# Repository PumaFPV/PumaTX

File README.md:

# PumaTX

THIS README IS NOT UP TO DATE

# Introduction:
This is a try to build my own FPV remote controller based on ESP32 (nRF52 later on) and DJI GL200A for its compactness and format.

# Release Candidates:

RC04: 
	Software:
		PPM
		SBus
		Hall Effect
		Pots reading (Left pot mode switch left = down ; Right = up ; RTH = overwrite)
		Arm reading
		Pre reading
		RTH reading
		Power on / off via sport switch
		basic screen use + vbat + splash screen
		
	Hardware:
		Micro USB (from controller)
		2S LiPo
		external RF (R9M)
		USB 2.0 (or 3.0 if I find one,) to plug in module (gnd, 5v, VBat, Tx)
		Support for JR module in phone holder
		
RC05:
	Software:
		Interupts for buttons (so code can run faster)
		MavLink (only rc, no telemetry) 
§		MavLink Bluetooth Passthrough (Uses to much memory, will have to sort it out for another release)
§		Choice between SBus and MavLink when compiling
		SoftPower use only interrupt
§		LED for power
		
	Hardware:
§		1S battery + USB charger + boost converter
§		MavLink module
		
RC06:
	Software:
		Menu Navigation
		
	Hardware:
		Turn on / off stuff (transistor & MOSFET)
		Fan
		Haptic
		
RC07:
	Software:
		Bluetooth HID
		
RC08:
	Software:
		MavLink telemetry screen

RC09:
	Software:
		CVBS Screen
		
	Hardware:
		USB 3.0 (5v, gnd, tx, rx, vid, 1, 2, VBat)
	
RC10:
	Hardware:
		Homemade PCB
		C1, C2
		Haptic
		
Other ideas:
	SPort
	FrSky X for bind / Rx num
	Sound output
	External bluetooth joystick
	Fix the calibration issue
	Remove screen loop
	eepron save
	
# Required specs:
-Read data from the hall effect MLX sensors from the controller

-Have 10 channels (can't do more cause of the limitation of the controller)

-Output SBus (to plug into R9M)

-Input SPort to read telemetry data (From R9M)

-Have a screen for minimal setup

-Have a Soft Power capabilty (using the power button from the controller)

This is the bare minimum. But I do have way more ideas coming.

# Folders:
In the "PumaTX_RC" folder you will find the different Release Candidate (Higher is better but could be unstable, read description for more details).

In the "Other" folder you will find different kind of "documentation" it is mostly here for my personnal use, as a reference.

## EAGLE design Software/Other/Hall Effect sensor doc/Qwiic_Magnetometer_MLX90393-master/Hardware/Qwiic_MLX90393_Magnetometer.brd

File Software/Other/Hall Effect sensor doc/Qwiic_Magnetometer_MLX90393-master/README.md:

SparkFun Qwiic Magnetometer MLX90393
========================================

[*SparkFun Qwiic Magnetometer MLX90393 (14571)*](https://www.sparkfun.com/products/14571)

The SparkFun MLX90393 Magnetometer Breakout is a triple-axis magnetic sensor board capable of sensing very small fields (like the Earth’s magnetic field), while still behaving as one would expect during saturation in larger fields (like a nearby magnet). The MLX90393 breakout can be used as a compass sensor but also works well as a non-contact controller, a flow meter with a magnetic impeller, or a linear actuator position sensor. To make it even easier to to get your readings, all communication is enacted exclusively via I2C, utilizing our handy Qwiic system. However, we still have broken out 0.1"-spaced pins in case you prefer to use a breadboard.

Repository Contents
-------------------

* **/Hardware** - Eagle design files (.brd, .sch)
* **/Production** - Production panel files (.brd)
* **/Software** - Example Code

Documentation
--------------
* **[Arduino Library](https://github.com/tedyapo/arduino-MLX90393)** - Arduino library MLX90393 magnetometer sensor.
* **[Hookup Guide](https://learn.sparkfun.com/tutorials/qwiic-magnetometer-mlx90393-hookup-guide)** - Basic hookup guide for the SparkFun Qwiic Magnetometer MLX90393.
* **[SparkFun Fritzing repo](https://github.com/sparkfun/Fritzing_Parts)** - Fritzing diagrams for SparkFun products. 

License Information
-------------------

This product is _**open source**_! 

Please review the LICENSE.md file for license information. 

If you have any questions or concerns on licensing, please contact techsupport@sparkfun.com.

Distributed as-is; no warranty is given.

- Your friends at SparkFun.

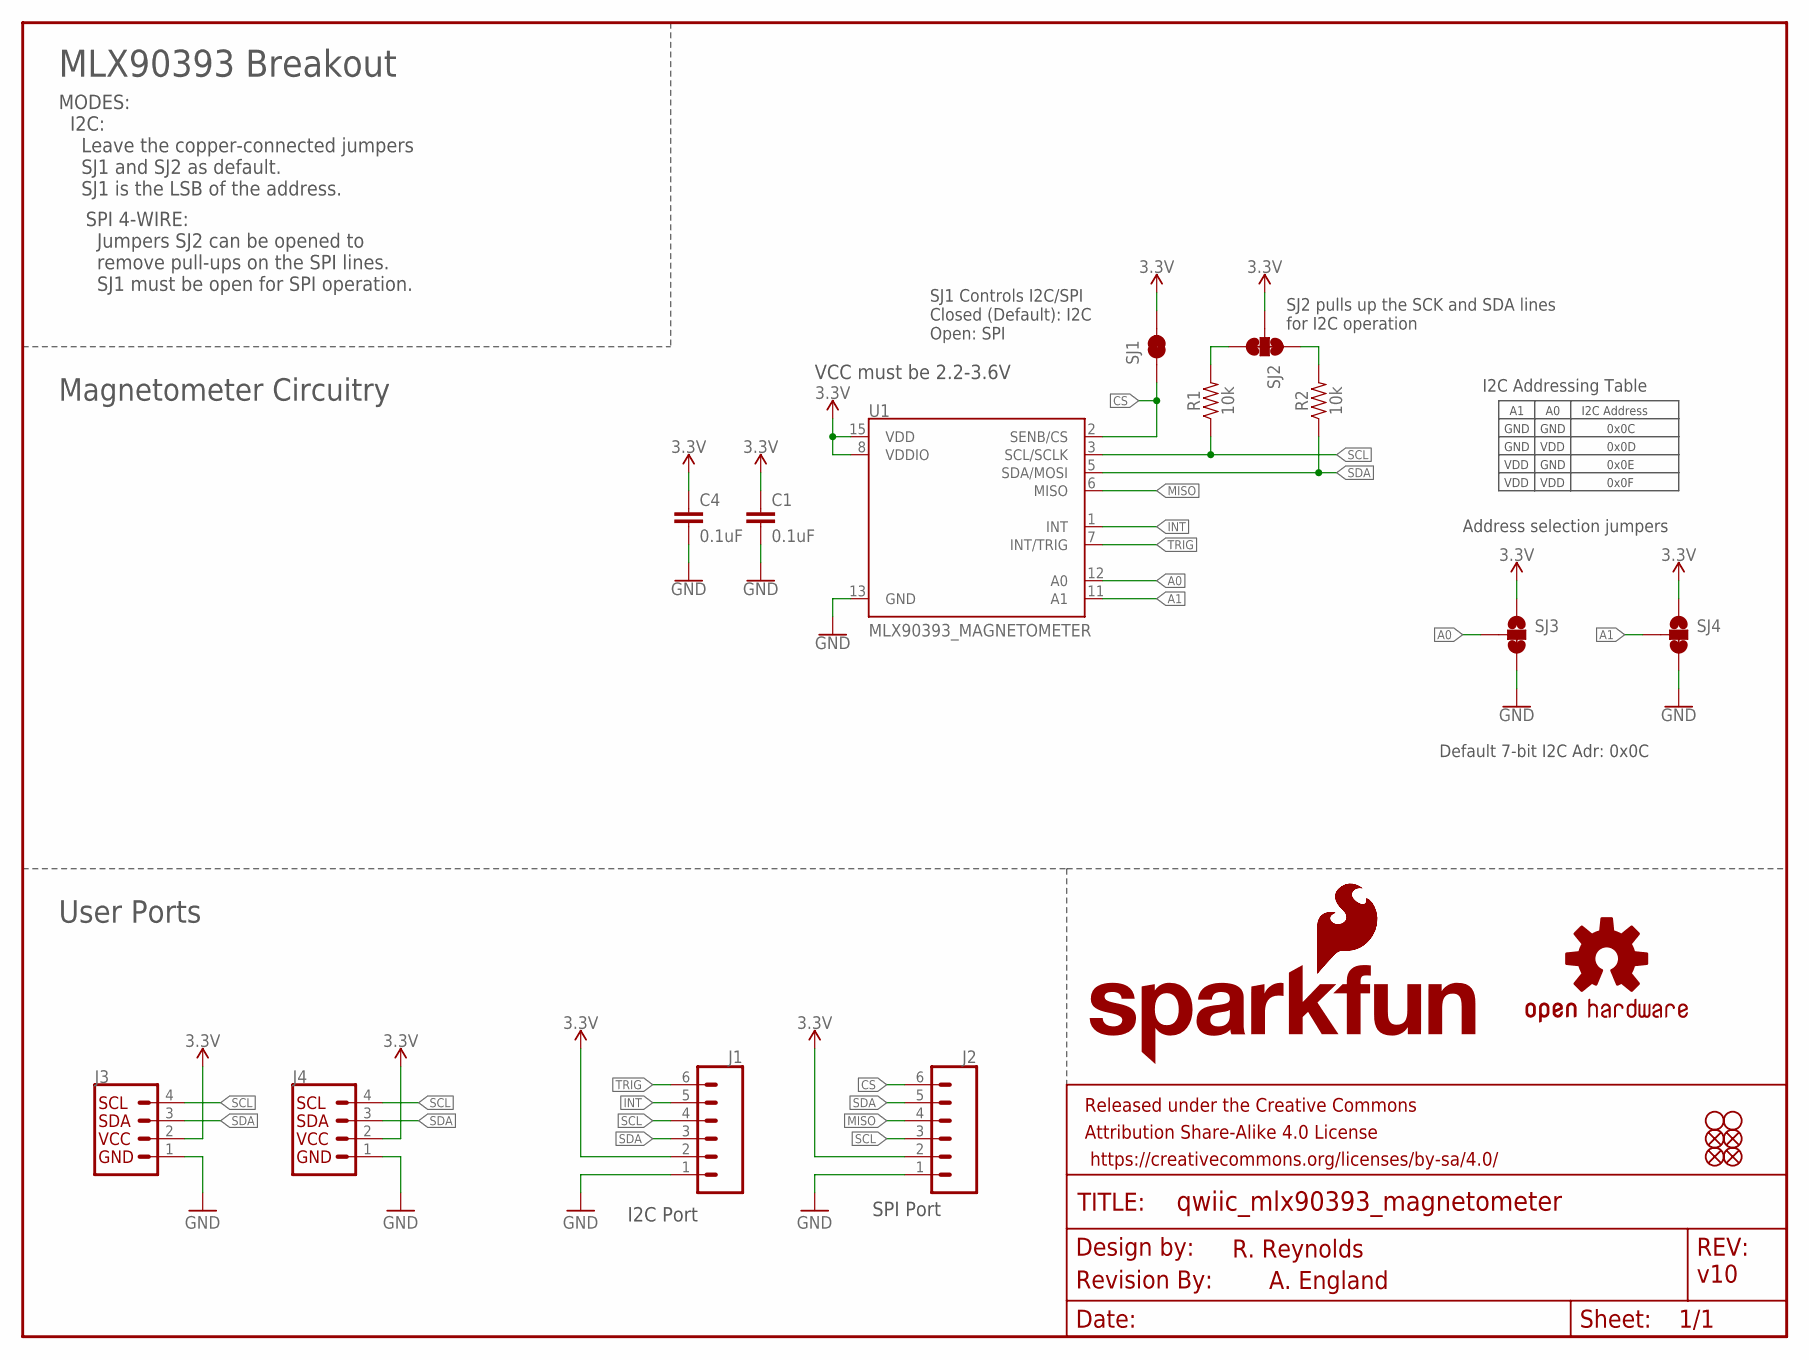
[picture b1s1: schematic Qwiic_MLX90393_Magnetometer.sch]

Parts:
C1, C4: 0.1uF; 0603
FD1, FD2, FD3, FD4: FIDUCIALUFIDUCIAL; FIDUCIAL-MICRO
FRAME2: FRAME-LETTER; CREATIVE_COMMONS
J1, J2: CONN_06NO_SILK_FEMALE_PTH; 1X06_NO_SILK
J3, J4: QWIIC_CONNECTORJS-1MM; 1X04_1MM_RA
JP3, JP4: STAND-OFF
LOGO1: SFE_LOGO_NAME_FLAME.1_INCH; SFE_LOGO_NAME_FLAME_.1
LOGO2: SFE_LOGO_FLAME.1_INCH; SFE_LOGO_FLAME_.1
LOGO3: REVISION
R1, R2: 10k; 0603
SJ1: JUMPER-SMT_2_NC_TRACE_SILK; SMT-JUMPER_2_NC_TRACE_SILK
SJ2: JUMPER-PAD-3-NC_BY_TRACE; PAD-JUMPER-3-3OF3_NC_BY_TRACE_YES_SILK_FULL_BOX
SJ3, SJ4: JUMPER-SMT_3_1-NC_TRACE_SILK; SMT-JUMPER_3_1-NC_TRACE_SILK
U1: MLX90393_MAGNETOMETER; QFN-16_WITH_AXIES
U$1: OSHW-LOGOS; OSHW-LOGO-S

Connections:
3.3V: C1.1, C4.1, J1.2, J2.2, J3.2, J4.2, SJ1.2, SJ2.2, SJ3.1, SJ4.1, U1.8 (VDDIO), U1.15 (VDD)
A0: SJ3.2, U1.12 (A0)
A1: SJ4.2, U1.11 (A1)
CS: J2.6, SJ1.1, U1.2 (SENB/CS)
GND: C1.2, C4.2, J1.1, J2.1, J3.1, J4.1, SJ3.3, SJ4.3, U1.13 (GND)
INT: J1.5, U1.1 (INT)
MISO: J2.4, U1.6 (MISO)
unnamed: R2.2, SJ2.1
unnamed: R1.2, SJ2.3
SCL: J1.4, J2.3, J3.4, J4.4, R1.1, U1.3 (SCL/SCLK)
SDA: J1.3, J2.5, J3.3, J4.3, R2.1, U1.5 (SDA/MOSI)
TRIG: J1.6, U1.7 (INT/TRIG)

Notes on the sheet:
Address selection jumpers
v10
R. Reynolds
MLX90393 Breakout
SJ2 pulls up the SCK and SDA lines for I2C operation
MODES: I2C: Leave the copper-connected jumpers SJ1 and SJ2 as default. SJ1 is the LSB of the address.
Magnetometer Circuitry
User Ports
VCC must be 2.2-3.6V
SJ1 Controls I2C/SPI Closed (Default): I2C Open: SPI
I2C Port
SPI Port
I2C Address
0x0C
0x0D
0x0E
0x0F
GND
VDD
SPI 4-WIRE: Jumpers SJ2 can be opened to remove pull-ups on the SPI lines. SJ1 must be open for SPI operation.
I2C Addressing Table
Default 7-bit I2C Adr: 0x0C
A. England

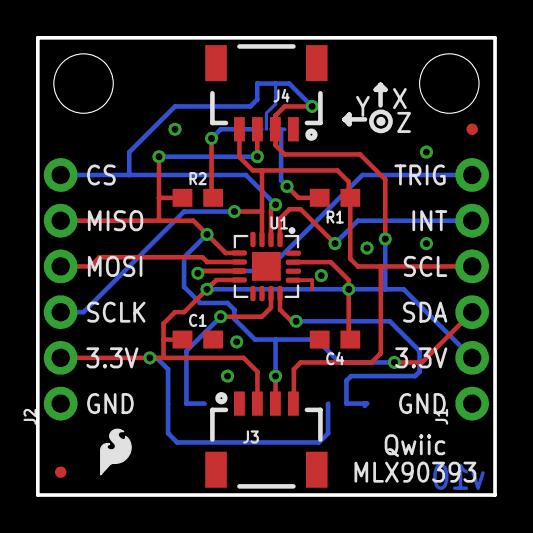
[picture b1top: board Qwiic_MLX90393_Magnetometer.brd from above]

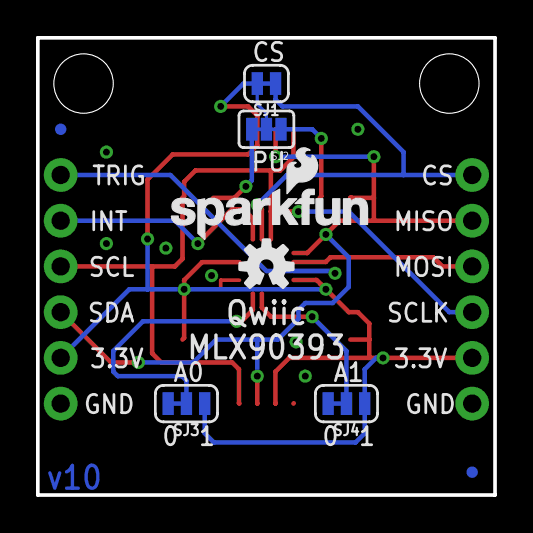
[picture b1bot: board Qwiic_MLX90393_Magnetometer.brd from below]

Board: 2 copper layers, 25.4 x 25.4 mm, 24 parts (8 on the bottom side), 12 nets.

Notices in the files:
parts and their libraries:
SparkFun-Aesthetics: Licensing: Creative Commons ShareAlike 4.0 International - https://creativecommons.org/licenses/by-sa/4.0
SparkFun-Aesthetics: Released under the Creative Commons Attribution Share-Alike 4.0 License
SparkFun-Aesthetics: https://creativecommons.org/licenses/by-sa/4.0
